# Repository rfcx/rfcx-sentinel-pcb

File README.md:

#RFCx Sentinel PCB
@gibsjose @jesse-millwood @rfcx

##Description
This repository contains the **KiCAD** project and related libraries for the RFCx PCB designed by Jesse Millwood and Joe Gibson for the GVSU (Grand Valley State University) RFCx Senior Project design, *Project Necromancer*. This project has been continued by Jesse Millwood and Joe Gibson after they graduated and has since been renamed *RFCx Sentinel*. 

This repository is for the main board that includes the following functionality:
- Buck/Boost input voltage to charge phone
- Regulate input power 3.3V to run the logic on the board
- Charge two Lithium Ion Batteries
- Take local measurements such as voltage, current, temperature, and humidity
- Relay information to the phone via a USB interface
- An experimental breakaway board for microphone filtering

This README is meant to be a user guide for the **REV 3** main board. 

###Revision Overview
Rev1 of the board was a single board and was designed for one particular off-the-shelf enclosure.
Rev2 of the design is a modular design in order to introduce a degree of flexibility to the design. This revision included an MPPT board and main board.
Rev3 of the design will keep the modular design, however new components will be chosen based on testing of Rev2. This revision is just the main board.

##Physical Install Instructions
The enclosure that is being used is the Polycase WP-33. The installer must take into consideration where the interfacing wires will be in relation to the other board. A list of interfacing wires that must be considered are:
* **Main Board:** Power from the panels.
* **Main Board:** 2 JST connectors that go from the batter charging circuitry to the batteries
* **Main Board:** 2 JST connectors that interface to the NTC thermocouple. This thermocouple is meant to be glued or attached to the batteries.
* **Main Board:** 1 USBA to microUSB connector to the phone
Once the hardware connections are made it will be a good idea to ensure that the phone has the proper software installed such as the proper ROM and version of the Gaurdian app. For phone software refer to the [RFCx Guardian App](https://github.com/rfcx/rfcx-guardian-android) github page.

##Outline of Directories
.  
├── Images  
│   ├── *Contains Images for the README*  
├── Kicad Project  
│   ├── Graphics  
│   │   ├── *Contains Graphics for the silk screen layer*  
│   ├── Graphics.pretty  
│   │   ├── *Contains `.kicad_mod` files to be placed on the silk screen layer*  
│   └── Main  
│       ├── *Contains schematic files (`.sch`) for the main board  
│       ├── Fabrication  
│       │   └── *Contains files for fabrication (Gerbers, BOM, Position, PDF)*  
│       │       Gerbers  
│       │       ├── *Contains Gerbers for the board manufacturers*  
│       │       Position  
│       │       ├── Inches  
│       │       │   ├── *Contains position file for top and bottom layers in inches*  
│       │       └── mm  
│       │           └── *Contains position file for top and bottom layers in mm*  
│       RFCx.pretty  
│       ├── *Contains module (footprint) files for components that needed to be made*  
│       Local-Libs  
│       └── *Contains schematic part libraries for parts that were made for this project*  
└── LICENSE  

## How to use this repository
1. Install KiCAD(4.0+) (http://kicad-pcb.org/download/)
2. clone the libraries and checkout a specific version
``` sh
mkdir -p ~/build
cd ~/build
git clone https://github.com/KiCad/kicad-library.git
cd kicad-library
git checkout 3c84dba8e473a325a17eae25ed3203d949589c10
mkdir build
cd build
cmake ..
make
make install
```
- A specific version of the KiCAD schematic libraries is used because sometimes they change. It is just safer to stick with one version though so there is little to no need to mess with the schematic symbols later
3. Download KiCAD footprints
4. Open the KiCAD application and load the project file.
- `File`-> `Open Project`
5. Open the `Mainboard.sch` file.
6. Tell KiCAD where the schematic symbol libraries are
- `Preferences`->`Component Libraries`
- Click the lower `Add` button and search for the `Local-Libs` directory if not already listed in the bottom pane of the window.
- Click the upper `Add` button and change to the `Local-Libs` directory. Select all of the `.lib` files and hit `Open`
- Click `Okay`

## Conventions for this project
- **Schematic Libraries:** The symbols in the `Local-Libs` libraries are to be used first. This is because I like how these symbols look. If the symbol is not there, use the symbols in `kicad-library`. If the symbol you are looking for isn't in any of those, make it your self, add it to the `Local-Libs` and make not of it in a pull request.
- **Footprint Libraries:** 
- **PCB Canvas:** Editing of the PCB should be done in the GAL mode of `pcbnew`. This is because some things are handled slightly differently in the other canvases.
- **
- **Units:** Use Imperial units when editing/laying out so an object/trace is not located at some odd fraction of an inch.

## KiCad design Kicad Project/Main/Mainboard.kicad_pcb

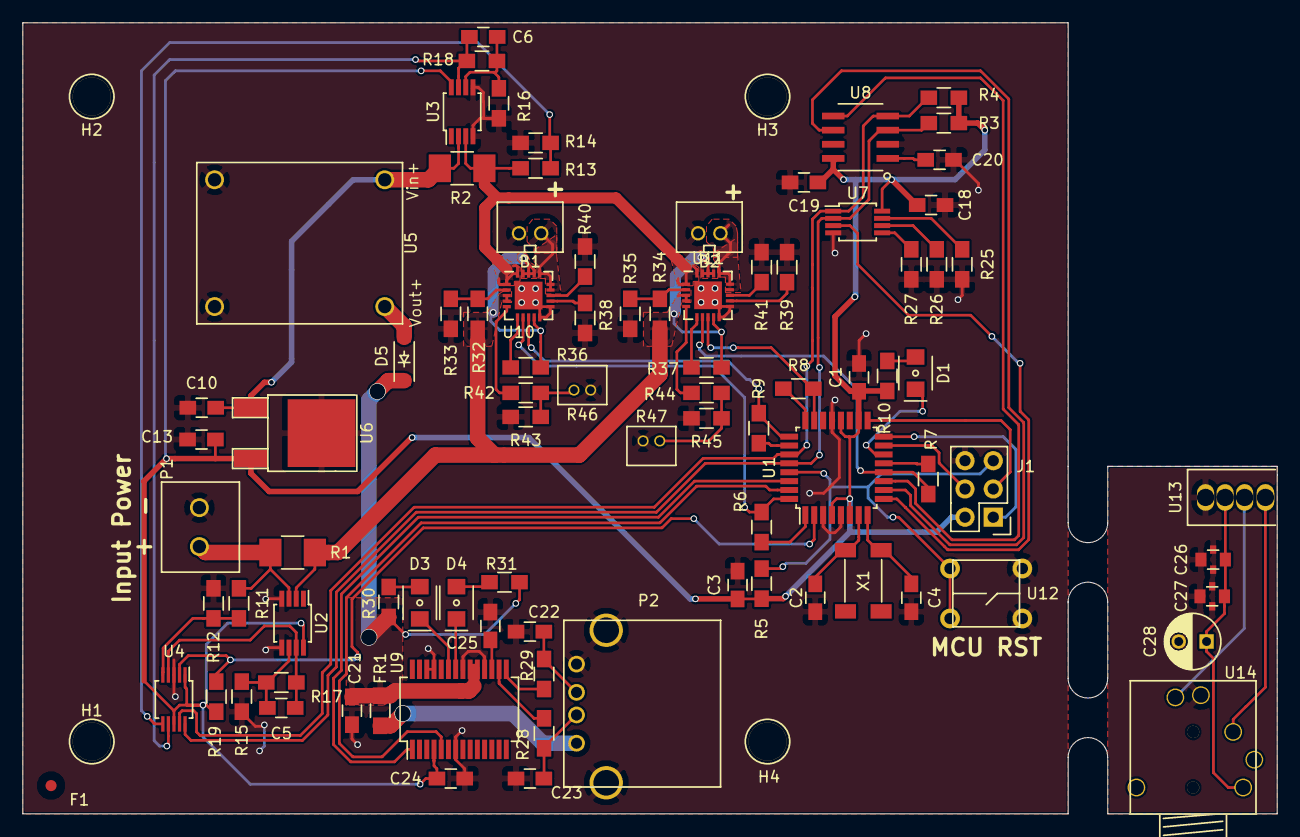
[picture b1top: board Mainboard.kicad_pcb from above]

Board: 2 copper layers, 112.8 x 71.1 mm, 91 parts (0 on the bottom side), 69 nets.

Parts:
B1, B2: Li-ion-2Cell-Conn; JST-2mm
C1, C3, C10, C13: 1uF; C_0805_HandSoldering
C2, C4: 6pF; C_0805_HandSoldering
C5, C6, C18, C20, C21, C24, C25: 0.1uF; C_0805_HandSoldering
C19: 0.22uF; C_0805_HandSoldering
C22, C23: 47pF; C_0805_HandSoldering
C26, C27: Cap-X2Y; C_0805_X2Y
C28: DNP; C_Radial_D5_L6_P2.5
D1: LED; LED-1208
D3: GRN; LED-1208
D4: YLW; LED-1208
D5: RB161M-20; SOD-123
F1: Fiducial; Fiducial_1mm_Dia_2.54mm_Outer_CopperTop
FR1: Ferrite; R_0805_HandSoldering
H1, H2, H3, H4: Mounting_Hole; Mnt_Hole
J1: ICSP; Pin_Header_Straight_2x03
P1: CONN_01X02; TerminalBlock_2
P2: USB_A
R1, R2: 0.51, 1W; R_1210_HandSoldering
R3, R4: 4.7k; R_0805_HandSoldering
R5, R19, R25, R26, R27, R43, R45: 10k; R_0805_HandSoldering
R6, R7, R8, R9, R36, R37, R42, R44: 1k; R_0805_HandSoldering
R10: 730; R_0805_HandSoldering
R11, R13: 1540; R_0805_HandSoldering
R12, R14: 2100; R_0805_HandSoldering
R15, R16: 200k; R_0805_HandSoldering
R17, R18: 2550; R_0805_HandSoldering
R28, R29: 27; R_0805_HandSoldering
R30, R31: 270; R_0805_HandSoldering
R32, R34: 270k; R_0805_HandSoldering
R33, R35, R38, R39: 100k; R_0805_HandSoldering
R40, R41: 1.14k; R_0805_HandSoldering
R46, R47: NTC; JST-1.5mm
U1: ATmega328P; TQFP-32_7x7mm_Pitch0.8mm
U2, U3: LTC6800; MSOP-8_3x3mm_Pitch0.65mm
U4: ADS1015; MSOP-10_3x3mm_Pitch0.5mm
U5: DC-DC_Boost_Module
U6: SM72238; TO-252-2Lead
U7: LM75BDP; MSOP-8_3x3mm_Pitch0.65mm
U8: HIH6130; HIH-SOIC-8
U9: FT232R; SSOP-28_5.3x10.2mm_Pitch0.65mm
U10, U11: MCP73871; QFN-20-1EP_4x4mm_Pitch0.5mm
U12: Button_SPST_4; SPST_4
U13: 3.5mm-Male-TH; Audio_3.5mm_Male_TH
U14: 3.5mm-Female-TH; Audio_3.5mm_Feale_TH
X1: 32kHz; SOJ-4

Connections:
+3V3: C1.1, C3.1, C13.1, C18.1, C19.1, C24.1, J1.2, R3.1, R4.1, R5.1, R10.1, R19.1, U1.4, U1.6, U1.18, U1.20, U2.8, U3.8, U4.1, U4.8, U6.3, U7.8, U8.8, U9.4
+5V: C21.1, D5.1, FR1.1, R30.1, R31.1, U9.19, U9.20
/ADC/Input-Current-H: P1.1, R1.1, R11.1, U2.3
/ADC/Output-Current-L: C10.1, R2.1, U3.2, U5.3, U6.1
/Battery Charging/Bat-In: R1.2, R32.1, R34.1, R36.1, R37.1, U2.2, U10.3, U10.4, U10.9, U10.17, U10.18, U10.19, U11.3, U11.4, U11.9, U11.17, U11.18, U11.19
/Battery Charging/Bat-Out: R2.2, R13.1, U3.3, U10.1, U10.20, U11.1, U11.20
/Environment Sensors/ENV_AL_H: U1.11, U8.5
/Environment Sensors/ENV_AL_L: U1.10, U8.6
/Environment Sensors/ENV_OS: U1.9, U7.3
/Microcontroller/AT-Alert: R19.2, U1.2, U4.2
/Microcontroller/AT-BAT1-STAT1: R9.2, U1.25, U10.8
/Microcontroller/AT-BAT1-STAT2: R6.2, U1.32, U10.7
/Microcontroller/AT-BAT2-STAT1: R8.2, U1.23, U11.8
/Microcontroller/AT-BAT2-STAT2: R7.2, U1.12, U11.7
/Microcontroller/AT-RXD: U1.30, U9.1
/Microcontroller/AT-SCL: R3.2, U1.28, U4.10, U7.2, U8.3
/Microcontroller/AT-SDA: R4.2, U1.27, U4.9, U7.1, U8.4
/Microcontroller/AT-TXD: U1.31, U9.5
GND: B1.1, B2.1, C1.2, C2.2, C3.2, C4.2, C10.2, C13.2, C18.2, C19.2, C20.2, C21.2, C22.2, C23.2, C24.2, C25.2, C26.2, C26.3, C26.4, C27.2, C27.3, C27.4, C28.2, J1.6, P1.2, P2.4, P2.5, R12.2, R14.2, R15.2, R16.2, R25.1, R26.2, R27.2, R33.2, R35.2, R38.2, R39.2, R40.2, R41.2, R43.2, R45.2, R46.2, R47.2, U1.3, U1.5, U1.21, U2.4, U2.5, U3.4, U3.5, U4.3, U5.1, U5.4, U6.2, U7.4, U8.2, U9.7, U9.18, U9.21, U9.25, U9.26, U10.10, U10.11, U10.21, U11.10, U11.11, U11.21, U12.1, U12.2, U13.4, U14.1
unnamed: B1.2, U10.14, U10.15, U10.16
unnamed: B2.2, U11.14, U11.15, U11.16
unnamed: C2.1, U1.7, X1.1
unnamed: C4.1, U1.8, X1.4
unnamed: C5.1, R15.1, R17.1, U2.6
unnamed: C5.2, R17.2, U2.7, U4.4
unnamed: C6.1, R16.1, R18.1, U3.6
unnamed: C6.2, R18.2, U3.7, U4.7
unnamed: C20.1, U8.1
unnamed: C22.1, P2.3, R29.1
unnamed: C23.1, P2.2, R28.1
unnamed: C25.1, U9.17
unnamed: C26.1, C27.1, C28.1, U13.3, U14.4
unnamed: D1.1, U1.14
unnamed: D1.2, R10.2
unnamed: D3.1, U9.23
unnamed: D3.2, R30.2
unnamed: D4.1, U9.22
unnamed: D4.2, R31.2
unnamed: D5.2, U5.2
unnamed: FR1.2, P2.1
unnamed: J1.1, U1.16
unnamed: J1.3, U1.17
unnamed: J1.4, U1.15
unnamed: J1.5, R5.2, U1.29, U12.3, U12.4
unnamed: R6.1, U1.1
unnamed: R7.1, U1.13
unnamed: R8.1, U1.24
unnamed: R9.1, U1.26
unnamed: R11.2, R12.1, U4.5
unnamed: R13.2, R14.1, U4.6
unnamed: R25.2, U7.7
unnamed: R26.1, U7.6
unnamed: R27.1, U7.5
unnamed: R28.2, U9.16
unnamed: R29.2, U9.15
unnamed: R32.2, R33.1, U10.2
unnamed: R34.2, R35.1, U11.2
unnamed: R36.2, U10.6
unnamed: R37.2, U11.6
unnamed: R38.1, U10.12
unnamed: R39.1, U11.12
unnamed: R40.1, U10.13
unnamed: R41.1, U11.13
unnamed: R42.1, U10.5
unnamed: R42.2, R43.1, R46.1
unnamed: R44.1, U11.5
unnamed: R44.2, R45.1, R47.1
unnamed: U13.1, U14.2
unnamed: U13.2, U14.3

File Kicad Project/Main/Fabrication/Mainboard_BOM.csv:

"Project:","Mainboard"
"Tool:","kicad"
"Number of Parts ","91"
" "," "
"Reference","Quantity","Value","Package","Distributor","Distributor #"
"F1","1","Fiducial","Fiducials:Fiducial_1mm_Dia_2.54mm_Outer_CopperTop","DigiKey","NA"
"C26,C27","2","Cap-X2Y","RFCx:C_0805_X2Y","DigiKey","709-1010-1-ND"
"C28","1","DNP","Capacitors_ThroughHole:C_Radial_D5_L6_P2.5","DigiKey","NA"
"C2,C4","2","6pF","Capacitors_SMD:C_0805_HandSoldering","DigiKey","311-1095-1-ND"
"C23,C22","2","47pF","Capacitors_SMD:C_0805_HandSoldering","DigiKey","1276-1832-1-ND"
"C5,C6,C20,C18,C24,C21,C25","7","0.1uF","Capacitors_SMD:C_0805_HandSoldering","DigiKey","399-1167-1-ND"
"C19","1","0.22uF","Capacitors_SMD:C_0805_HandSoldering","DigiKey","587-1287-1-ND"
"C3,C1,C13,C10","4","1uF","Capacitors_SMD:C_0805_HandSoldering","DigiKey","1276-1275-1-ND"
"U14","1","3.5mm-Female-TH","RFCx:Audio_3.5mm_Feale_TH","DigiKey","CP-435107-ND"
"FR1","1","Ferrite","Resistors_SMD:R_0805_HandSoldering","DigiKey","587-1911-1-ND"
"R46,R47","2","NTC","RFCx:JST-1.5mm","DigiKey","BC2384-ND, 455-1657-ND"
"R2,R1","2","0.51, 1W","Resistors_SMD:R_1210_HandSoldering","DigiKey","RCWE.51FCT-ND"
"R29,R28","2","27","Resistors_SMD:R_0805_HandSoldering","DigiKey","P27ACT-ND"
"R30,R31","2","270","Resistors_SMD:R_0805_HandSoldering","DigiKey","311-270CRCT-ND"
"R10","1","730","Resistors_SMD:R_0805_HandSoldering","DigiKey","P732CCT-ND"
"R8,R9,R7,R6,R36,R42,R37,R44","8","1k","Resistors_SMD:R_0805_HandSoldering","DigiKey","P1.0KACT-ND"
"R40,R41","2","1.14k","Resistors_SMD:R_0805_HandSoldering","DigiKey","P1.15KCCT-ND"
"R11,R13","2","1540","Resistors_SMD:R_0805_HandSoldering","DigiKey","P1.54KCCT-ND"
"R12,R14","2","2100","Resistors_SMD:R_0805_HandSoldering","DigiKey","P2.10KCCT-ND"
"R17,R18","2","2550","Resistors_SMD:R_0805_HandSoldering","DigiKey","311-2.55KCRCT-ND"
"R3,R4","2","4.7k","Resistors_SMD:R_0805_HandSoldering","DigiKey","311-4.70KCRCT-ND"
"R5,R19,R25,R26,R27,R43,R45","7","10k","Resistors_SMD:R_0805_HandSoldering","DigiKey","P10KACT-ND"
"R38,R33,R39,R35","4","100k","Resistors_SMD:R_0805_HandSoldering","DigiKey","RHM100KCHCT-ND"
"R15,R16","2","200k","Resistors_SMD:R_0805_HandSoldering","DigiKey","P200KACT-ND"
"R32,R34","2","270k","Resistors_SMD:R_0805_HandSoldering","DigiKey","P270KCCT-ND"
"H1,H2,H3,H4","4","Mounting_Hole","RFCX:Mnt_Hole","DigiKey","NA"
"U13","1","3.5mm-Male-TH","RFCx:Audio_3.5mm_Male_TH","DigiKey","839-1239-ND"
"D1","1","LED","RFCx:LED-1208","DigiKey","160-1404-1-ND"
"D5","1","RB161M-20","Diodes_SMD:SOD-123","DigiKey","RB161M-20CT-ND"
"D3","1","GRN","RFCx:LED-1208","DigiKey","350-2885-ND"
"D4","1","YLW","RFCx:LED-1208","DigiKey","511-1275-1-ND"
"P1","1","CONN_01X02","RFCX:TerminalBlock_2","DigiKey","ED2740-ND"
"U1","1","ATmega328P","Housings_QFP:TQFP-32_7x7mm_Pitch0.8mm","DigiKey","ATMEGA328P-AU-ND"
"J1","1","ICSP","Pin_Headers:Pin_Header_Straight_2x03","DigiKey","S2011EC-03-ND"
"U12","1","Button_SPST_4","RFCx:SPST_4","DigiKey","450-1650-ND"
"U2,U3","2","LTC6800","Housings_SSOP:MSOP-8_3x3mm_Pitch0.65mm","DigiKey","LTC6800HMS8#PBF-ND"
"U4","1","ADS1015","Housings_SSOP:MSOP-10_3x3mm_Pitch0.5mm","DigiKey","296-25227-1-ND"
"U6","1","SM72238","TO_SOT_Packages_SMD:TO-252-2Lead","DigiKey","296-39811-5-ND "
"U5","1","DC-DC_Boost_Module","RFCx:DC-DC_Boost_Module","DigiKey","NA"
"U7","1","LM75BDP","Housings_SSOP:MSOP-8_3x3mm_Pitch0.65mm","DigiKey","568-4768-1-ND"
"U8","1","HIH6130","RFCx:HIH-SOIC-8","DigiKey","480-3651-1-ND "
"P2","1","USB_A","Connect:USB_A","DigiKey","UE27AC54100-ND"
"U9","1","FT232R","Housings_SSOP:SSOP-28_5.3x10.2mm_Pitch0.65mm","DigiKey","768-1007-1-ND"
"U10,U11","2","MCP73871","Housings_DFN_QFN:QFN-20-1EP_4x4mm_Pitch0.5mm","DigiKey","MCP73871-2CCI/ML-ND"
"B1,B2","2","Li-ion-2Cell-Conn","RFCx:JST-2mm","DigiKey","455-1704-ND"
"X1","1","32kHz","RFCX:SOJ-4","DigiKey","300-8744-1-ND"

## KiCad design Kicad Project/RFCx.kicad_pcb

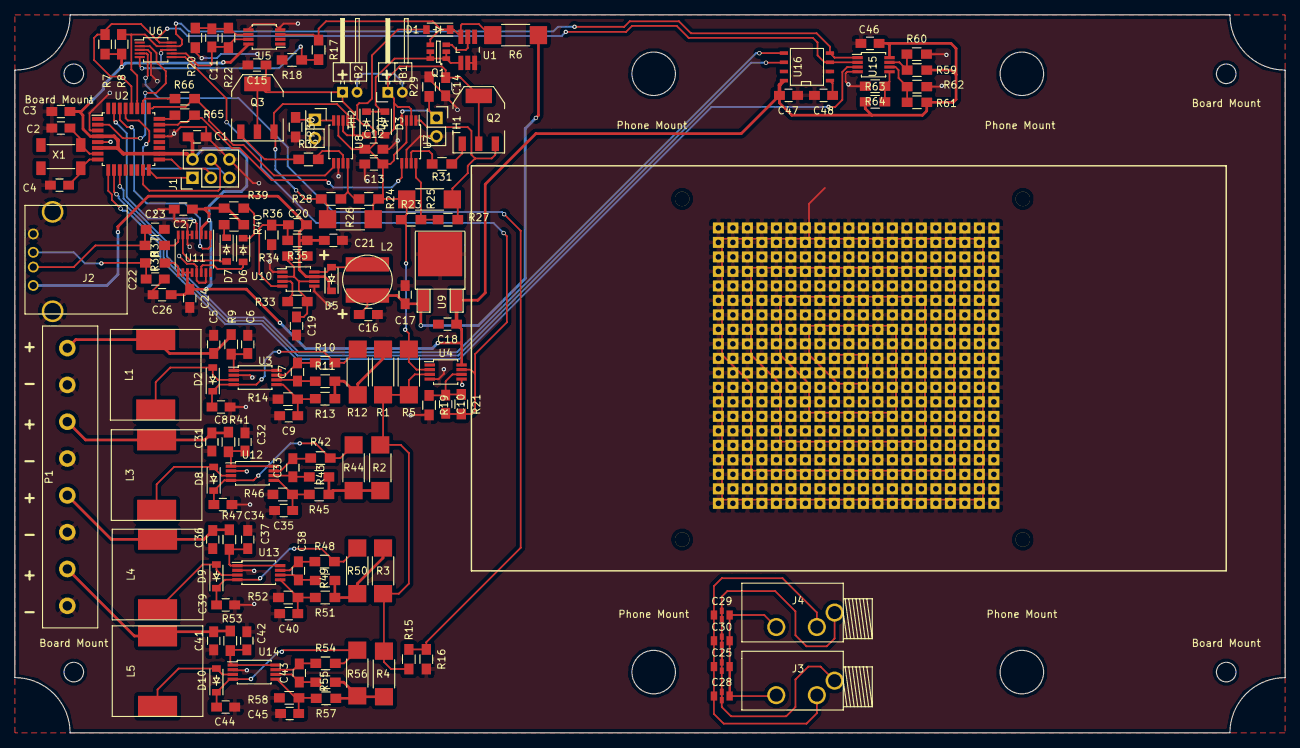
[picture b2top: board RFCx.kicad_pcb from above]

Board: 2 copper layers, 175.3 x 99.1 mm, 167 parts (1 on the bottom side), 96 nets.

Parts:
B1, B2: Li-ion(2Cell); Pin_Header_Angled_1x02
Board Mount: MountingHole_2-7mm
Board Mount#2, Board Mount#3, Board Mount#4: MountingHole_2-7mm
C1, C3, C7, C17, C18, C19, C33, C38, C43: 1uF; C_0805_HandSoldering
C2, C4: 10pF; C_0805_HandSoldering
C5, C6, C31, C32, C36, C37, C41, C42: 10uF; C_0805_HandSoldering
C8, C34, C39, C44: 22uF; C_0805_HandSoldering
C9, C35, C40, C45: 1nF; C_0805_HandSoldering
C10, C11, C12, C13, C14, C15, C46: 0.1uF; C_0805_HandSoldering
C16: 22uF Tant; C_0805_HandSoldering
C20: 39pF; C_0805_HandSoldering
C21: 68uF Tant; C_0805_HandSoldering
C22, C23: 47pF; C_0805_HandSoldering
C24, C26: 100nF; C_0805_HandSoldering
C25, C30: 0.1uF; X2Y
C27: 4.7uF; C_0805_HandSoldering
C28, C29: 1uF; X2Y
C47: 0.22uF; C_0805_HandSoldering
C48: 0.1; C_0805_HandSoldering
D1: 1N5819; SOD-123
D2, D3, D4, D5, D8, D9, D10: Diode-Shottky; SOD-123
D6: GRN; SOD-123
D7: LED; SOD-123
H1: Heatsink; HeatSink
J1: ICSP; Pin_Header_Straight_2x03
J2: USB; USB_A
J3, J4: Barrel; barrel-1-8
L1, L3, L4, L5: 27uH; Ind_12_5x12_5
L2: 6.8uH; Ind_6x6
P1: Terminal Block; Terminal_Block_8
Phone Mount: MountingHole_6mm
Phone Mount#2, Phone Mount#3, Phone Mount#4: MountingHole_6mm
Q1: FDC638; FDC-SOT-23-6
Q2, Q3: FZT788B; SOT-223
R1, R2, R3, R4: 0.025, 1W; R_2010_HandSoldering
R5, R6: 0.01,1W; R_2010_HandSoldering
R7, R8, R23, R24, R59, R60, R61, R62, R63, R64: 10k; R_0805_HandSoldering
R9, R10, R11, R31, R32, R41, R42, R43, R47, R48, R49, R53, R54, R55, R65, R66: 1k; R_0805_HandSoldering
R12, R44, R50, R56: 27.78, 1W; R_2010_HandSoldering
R13, R45, R51, R57: 2.32M; R_0805_HandSoldering
R14, R46, R52, R58: 845k; R_0805_HandSoldering
R15, R17: 1540; R_0805_HandSoldering
R16, R18: 2100; R_0805_HandSoldering
R19, R20, R33: 200k; R_0805_HandSoldering
R21: 2550; R_0805_HandSoldering
R22: Res; R_0805_HandSoldering
R25, R26: 0.2, 1W; R_2010_HandSoldering
R27, R28: 5k; R_0805_HandSoldering
R29, R30, R36: 49.9k; R_0805_HandSoldering
R34: 49.9; R_0805_HandSoldering
R35: 150k; R_0805_HandSoldering
R37, R38: 27; R_0805_HandSoldering
R39, R40: 730; R_0805_HandSoldering
TH1, TH2: NTC; Pin_Header_Straight_2x01
U1: LTC4412; TSOT-6-MK06A_Handsoldering
U2: ATmega328P; TQFP-32_7x7mm_Pitch0.8mm
U3, U12, U13, U14: SPV1040; TSSOP-8_4.4x3mm_Pitch0.65mm
U4, U5: LTC6800; MSOP-8_3x3mm_Pitch0.65mm
U6: ADS1015; MSOP-10_3x3mm_Pitch0.5mm
U7, U8: bq2057CTS; TSSOP-8_4.4x3mm_Pitch0.65mm
U9: SM72238; DPAK-2
U10: LMR61428; MSOP-8_3x3mm_Pitch0.65mm
U11: FT230X; SSOP-16_3.9x4.9mm_Pitch0.635mm
U15: LM75BDP; MSOP-8_3x3mm_Pitch0.65mm
U16: HIH6130; SOIC-8-N
X1: 32kHz; SOJ-4

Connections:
+3V3: C1.1, C3.1, C18.1, C24.1, C26.1, C27.1, C46.1, C47.1, J1.2, R7.1, R8.1, R39.1, R40.1, R59.1, R61.1, R63.1, U2.4, U2.6, U2.18, U4.8, U5.8, U6.8, U9.3, U11.3, U11.10, U11.11, U11.12, U15.8, U16.8
+5V: C20.1, C21.1, D5.1, J2.1, R34.1, R35.1, U10.7
/+3.3V and +5V Regulation/LM_FB: C20.2, R35.2, R36.1, U10.4
/+3.3V and +5V Regulation/Vin: C16.1, C17.1, L2.1, R6.1, U9.1
/ADC/Input-Current-H: R1.2, R2.2, R3.2, R4.2, R5.1, R15.1, U4.3
/ADC/Input-Current-L: C12.1, C13.1, D1.2, R5.2, R23.1, R24.1, R25.2, R26.2, U4.2, U7.3, U8.3
/ADC/Output-Current-H: D1.1, Q1.3, R6.2, R17.1, U1.6, U5.3
/Battery Management/Battery-Vout: D3.1, D4.1, Q1.1, U1.1
/Environment Sensors/ENV_AL_H: U2.11, U16.5
/Environment Sensors/ENV_AL_L: U2.10, U16.6
/Environment Sensors/ENV_OS: U2.9, U15.3
/MPPT1/MPPT-Vout: R1.1, R11.2, R12.2, R13.1
/MPPT1/Vin: C5.1, L1.1, P1.1, R9.1
/MPPT2/MPPT-Vout: R2.1, R43.2, R44.2, R45.1
/MPPT2/Vin: C31.1, L3.1, P1.3, R41.1
/MPPT3/MPPT-Vout: R3.1, R49.2, R50.2, R51.1
/MPPT3/Vin: C36.1, L4.1, P1.5, R47.1
/MPPT4/MPPT-Vout: R4.1, R55.2, R56.2, R57.1
/MPPT4/Vin: C41.1, L5.1, P1.7, R53.1
/Microcontroller/AT-Alert: U2.2, U6.2
/Microcontroller/AT-BAT1-STAT: R65.2, U2.23, U7.5
/Microcontroller/AT-BAT2-STAT: R66.2, U2.25, U8.5
/Microcontroller/AT-RXD: U2.30, U11.1
/Microcontroller/AT-SCL: R7.2, U2.28, U6.10, U15.2, U16.3
/Microcontroller/AT-SDA: R8.2, U2.27, U6.9, U15.1, U16.4
/Microcontroller/AT-TXD: U2.31, U11.4
/Phone Interface/Mic+: C25.1, C28.1, C29.1, C30.1, J3.3, J4.3
/Phone Interface/Mic-: C25.3, C28.3, C29.3, C30.3, J3.2, J4.2
/Phone Interface/MicShield: C25.2, C25.4, C28.2, C28.4, C29.2, C29.4, C30.2, C30.4, J3.1, J4.1
GND: B1.2, B2.2, C1.2, C2.2, C3.2, C4.2, C5.2, C6.2, C8.2, C9.2, C12.2, C13.2, C14.2, C15.2, C16.2, C17.2, C19.2, C21.2, C22.2, C23.2, C24.2, C26.2, C27.2, C31.2, C32.2, C34.2, C35.2, C36.2, C37.2, C39.2, C40.2, C41.2, C42.2, C44.2, C45.2, C46.2, C47.2, C48.2, H1.1, J1.6, J2.4, J2.5, J2.6, P1.2, P1.4, P1.6, P1.8, R14.2, R16.2, R18.2, R19.2, R20.2, R29.2, R30.2, R36.2, R46.2, R52.2, R58.2, R60.2, R62.2, R64.2, TH1.2, TH2.2, U1.2, U1.3, U2.3, U2.5, U2.21, U3.2, U4.4, U4.5, U5.4, U5.5, U6.3, U7.6, U8.6, U9.2, U10.1, U10.5, U11.5, U11.6, U11.13, U11.15, U12.2, U13.2, U14.2, U15.4, U16.2
unnamed: B1.1, C14.1, D3.2, Q2.2, Q2.4, U7.2
unnamed: B2.1, C15.1, D4.2, Q3.2, Q3.4, U8.2
unnamed: C2.1, U2.7, X1.1
unnamed: C4.1, U2.8, X1.4
unnamed: C6.1, R9.2, U3.1, U3.8
unnamed: C7.1, R11.1, U3.6
unnamed: C7.2, R10.1, U3.7
unnamed: C8.1, D2.1, R10.2, R12.1, U3.4
unnamed: C9.1, R13.2, R14.1, U3.5
unnamed: C10.1, R19.1, R21.1, U4.6
unnamed: C10.2, R21.2, U4.7, U6.6
unnamed: C11.1, R20.1, R22.1, U5.6
unnamed: C11.2, R22.2, U5.7, U6.7
unnamed: C19.1, R33.1, R34.2, U10.2, U10.6
unnamed: C22.1, J2.3, R38.1
unnamed: C23.1, J2.2, R37.1
unnamed: C32.1, R41.2, U12.1, U12.8
unnamed: C33.1, R43.1, U12.6
unnamed: C33.2, R42.1, U12.7
unnamed: C34.1, D8.1, R42.2, R44.1, U12.4
unnamed: C35.1, R45.2, R46.1, U12.5
unnamed: C37.1, R47.2, U13.1, U13.8
unnamed: C38.1, R49.1, U13.6
unnamed: C38.2, R48.1, U13.7
unnamed: C39.1, D9.1, R48.2, R50.1, U13.4
unnamed: C40.1, R51.2, R52.1, U13.5
unnamed: C42.1, R53.2, U14.1, U14.8
unnamed: C43.1, R55.1, U14.6
unnamed: C43.2, R54.1, U14.7
unnamed: C44.1, D10.1, R54.2, R56.1, U14.4
unnamed: C45.1, R57.2, R58.1, U14.5
unnamed: C48.1, U16.1
unnamed: D2.2, L1.2, U3.3
unnamed: D5.2, L2.2, U10.8
unnamed: D6.1, R39.2
unnamed: D6.2, U11.14
unnamed: D7.1, R40.2
unnamed: D7.2, U11.7
unnamed: D8.2, L3.2, U12.3
unnamed: D9.2, L4.2, U13.3
unnamed: D10.2, L5.2, U14.3
unnamed: J1.1, U2.16
unnamed: J1.3, U2.17
unnamed: J1.4, U2.15
unnamed: J1.5, U2.29
unnamed: Q1.2, U1.5
unnamed: Q2.1, R31.1
unnamed: Q2.3, R25.1, R27.2, U7.1
unnamed: Q3.1, R32.1
unnamed: Q3.3, R26.1, R28.2, U8.1
unnamed: R15.2, R16.1, U6.4
unnamed: R17.2, R18.1, U6.5
unnamed: R23.2, R27.1, U7.8
unnamed: R24.2, R28.1, U8.8
unnamed: R29.1, TH1.1, U7.4
unnamed: R30.1, TH2.1, U8.4
unnamed: R31.2, U7.7
unnamed: R32.2, U8.7
unnamed: R33.2, U10.3
unnamed: R37.2, U11.8
unnamed: R38.2, U11.9
unnamed: R59.2, R60.1, U15.7
unnamed: R61.2, R62.1, U15.6
unnamed: R63.2, R64.1, U15.5
unnamed: R65.1, U2.24
unnamed: R66.1, U2.26

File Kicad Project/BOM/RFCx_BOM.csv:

"Project:","RFCx"
"Tool:","kicad"
"Number of Parts ","159"
" "," "
"Reference","Quantity","Value","Package","Distributor","Distributor #"
"Q1","1","FDC638","RFCX:FDC-SOT-23-6","DigiKey","FDC638PCT-ND"
"C2,C4","2","10pF","Capacitors_SMD:C_0805_HandSoldering","DigiKey","709-1168-1-ND "
"C3,C1,C7,C19,C18,C17,C33,C38,C43","9","1uF","Capacitors_SMD:C_0805_HandSoldering","DigiKey","1276-1275-1-ND"
"C5,C6,C31,C32,C36,C37,C41,C42","8","10uF","Capacitors_SMD:C_0805_HandSoldering","DigiKey","587-1312-1-ND"
"C8,C34,C39,C44","4","22uF","Capacitors_SMD:C_0805_HandSoldering","DigiKey","1276-1822-1-ND "
"C9,C35,C40,C45","4","1nF","Capacitors_SMD:C_0805_HandSoldering","DigiKey","399-1147-1-ND"
"C10,C11,C12,C14,C13,C15,C30,C25,C46","9","0.1uF","Capacitors_SMD:C_0805_HandSoldering","DigiKey","311-1245-1-ND"
"Q2,Q3","2","FZT788B","SMD_Packages:SOT-223","DigiKey","FZT788BCT-ND"
"C16","1","22uF Tant","Capacitors_SMD:C_0805_HandSoldering","DigiKey","511-1506-1-ND"
"C20","1","39pF","Capacitors_SMD:C_0805_HandSoldering","DigiKey","1276-1769-1-ND"
"C21","1","68uF Tant","Capacitors_SMD:C_0805_HandSoldering","DigiKey","478-8414-1-ND"
"C27","1","4.7uF","Capacitors_SMD:C_0805_HandSoldering","DigiKey","1276-1065-1-ND"
"C26,C24","2","100nF","Capacitors_SMD:C_0805_HandSoldering","DigiKey","311-1245-1-ND"
"C23,C22","2","47pF","Capacitors_SMD:C_0805_HandSoldering","DigiKey","1276-1832-1-ND"
"C29,C28","2","1uF","RFCX:X2Y","DigiKey","709-1108-1-ND"
"C48","1","0.1","Capacitors_SMD:C_0805_HandSoldering","DigiKey","311-1245-1-ND"
"C47","1","0.22uF","Capacitors_SMD:C_0805_HandSoldering","DigiKey","587-1287-1-ND"
"R5,R6","2","0.01,1W","Resistors_SMD:R_2010_HandSoldering","DigiKey","RHM.010ASCT-ND"
"R7,R8,R23,R24,R60,R62,R64,R63,R61,R59","10","10k","Resistors_SMD:R_0805_HandSoldering","DigiKey","P10KACT-ND"
"R1,R2,R3,R4","4","0.025, 1W","Resistors_SMD:R_2010_HandSoldering","DigiKey","RHM.010ASCT-ND"
"R65,R66,R10,R11,R9,R31,R32,R42,R43,R41,R48,R49,R47,R54,R55,R53","16","1k","Resistors_SMD:R_0805_HandSoldering","DigiKey","P1.0KACT-ND "
"R12,R44,R50,R56","4","27.78, 1W","Resistors_SMD:R_2010_HandSoldering","DigiKey","RHM.010ASCT-ND"
"R13,R45,R51,R57","4","2.32M","Resistors_SMD:R_0805_HandSoldering","DigiKey","P6.65KCCT-ND"
"R14,R46,R52,R58","4","845k","Resistors_SMD:R_0805_HandSoldering","DigiKey","P2.10KCCT-ND "
"R15,R17","2","1540","Resistors_SMD:R_0805_HandSoldering","DigiKey","P1.54KCCT-ND"
"R16,R18","2","2100","Resistors_SMD:R_0805_HandSoldering","DigiKey","P2.10KCCT-ND"
"R21","1","2550","Resistors_SMD:R_0805_HandSoldering","DigiKey","311-2.55KCRCT-ND"
"R19,R20,R33","3","200k","Resistors_SMD:R_0805_HandSoldering","DigiKey","P200KACT-ND"
"R22","1","Res","Resistors_SMD:R_0805_HandSoldering","DigiKey","311-2.55KCRCT-ND"
"R25,R26","2","0.2, 1W","Resistors_SMD:R_2010_HandSoldering","DigiKey","989-1049-1-ND"
"R29,R30,R36","3","49.9k","Resistors_SMD:R_0805_HandSoldering","DigiKey","P49.9KCCT-ND"
"R27,R28","2","5k","Resistors_SMD:R_0805_HandSoldering","DigiKey","P4.99KCCT-ND "
"R34","1","49.9","Resistors_SMD:R_0805_HandSoldering","DigiKey","P49.9KCCT-ND"
"R35","1","150k","Resistors_SMD:R_0805_HandSoldering","DigiKey","P150KCCT-ND"
"R39,R40","2","730","Resistors_SMD:R_0805_HandSoldering","DigiKey","P732CCT-ND"
"R38,R37","2","27","Resistors_SMD:R_0805_HandSoldering","DigiKey","P27ACT-ND"
"X1","1","32kHz","RFCX:SOJ-4","DigiKey","300-8744-1-ND"
"L1,L3,L4,L5","4","27uH","RFCX:Ind_12_5x12_5","DigiKey","SRR1260-270MCT-ND"
"L2","1","6.8uH","RFCX:Ind_6x6","DigiKey","SRN6045-6R8YCT-ND "
"H1","1","Heatsink","RFCX:HeatSink","DigiKey","NA"
"D1","1","1N5819","Diodes_SMD:SOD-123","DigiKey","1N5819HW-FDICT-ND"
"D2,D3,D4,D5,D8,D9,D10","7","Diode-Shottky","Diodes_SMD:SOD-123","DigiKey","1N5819HW-FDICT-ND"
"D6","1","GRN","Diodes_SMD:SOD-123","DigiKey","754-1939-1-ND"
"D7","1","LED","Diodes_SMD:SOD-123","DigiKey","511-1293-1-ND"
"B1,B2","2","Li-ion(2Cell)","Pin_Headers:Pin_Header_Angled_1x02","DigiKey","455-1704-ND"
"P1","1","Terminal Block","RFCX:Terminal_Block_8","DigiKey","ED2615-ND"
"U1","1","LTC4412","Housings_SOT-23_SOT-143_TSOT-6:TSOT-6-MK06A_Handsoldering","DigiKey","LTC4412ES6#TRPBFCT-ND"
"U2","1","ATmega328P","Housings_QFP:TQFP-32_7x7mm_Pitch0.8mm","DigiKey","ATMEGA328P-AU-ND"
"J1","1","ICSP","Pin_Headers:Pin_Header_Straight_2x03","DigiKey","S2011EC-03-ND"
"U3,U12,U13,U14","4","SPV1040","Housings_SSOP:TSSOP-8_4.4x3mm_Pitch0.65mm","DigiKey","NA"
"U4,U5","2","LTC6800","SSOP:MSOP-8_3x3mm_Pitch0.65mm","DigiKey","LTC6800HMS8#PBF-ND"
"U6","1","ADS1015","Housings_SSOP:MSOP-10_3x3mm_Pitch0.5mm","DigiKey","296-25227-1-ND"
"U7,U8","2","bq2057CTS","SSOP:TSSOP-8_4.4x3mm_Pitch0.65mm","DigiKey","296-25916-1-ND"
"TH1,TH2","2","NTC","Pin_Headers:Pin_Header_Straight_2x01","DigiKey","BC2384-ND"
"U10","1","LMR61428","SSOP:MSOP-8_3x3mm_Pitch0.65mm","DigiKey","LMR61428XMM/NOPBCT-ND"
"U9","1","SM72238","SMD_Packages:DPAK-2","DigiKey","296-39811-5-ND "
"U11","1","FT230X","Housings_SSOP:SSOP-16_3.9x4.9mm_Pitch0.635mm","DigiKey","768-1135-1-ND"
"J2","1","USB","Connect:USB_A","DigiKey","UE27AC54100-ND"
"J3,J4","2","Barrel","RFCX:barrel-1-8","DigiKey","SC1460-ND"
"U15","1","LM75BDP","SSOP:MSOP-8_3x3mm_Pitch0.65mm","DigiKey","568-4768-1-ND"
"U16","1","HIH6130","SMD_Packages:SOIC-8-N","DigiKey","480-3651-1-ND "

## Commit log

2015-05-17 Modified gitignore for KiCad (it was for Eagle), and updated the README
2015-05-17 Added 3D files, local libraries (Jesse's libraries), and the .pretty project files
2015-05-17 Added Application Notes and Components; PDFs describing each component and how to use them
2015-05-17 Adding KiCad project
2015-05-17 Added some previews of the PCB and updated the README
2015-07-13 Revision 2
2015-08-03 Updated hardware files from August 3 2015 Updated README
2015-08-16 Removed the TI battery management circuits and the LT power path management This was replaced with a microchip battery management IC to handle the power path management/load sharing and battery charg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
2015-08-31 Produced Fabircation outputs Finished RevC of Main board Removed MPPT Board from Kicad Project
2015-08-31 Version 3
2015-08-31 Created third revison of the mainboard Created manufacturing files for the mainboard Deleated the MPPT board project
2015-11-28 Revision 3 of Sentinal PCB major changes: - This is one PCB now - The MPPT circuitry has been taken off - Libraries have been moved around - The FTDI FT232R is being used - A buck boost regulator is 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
2015-11-30 Rev 3.1 - Added microphone filter schematic and board - Added new silkscreen identifiers - Added Reset button for microcontroller - Fixed Address pin on ADS1015, pulled it up - Created new Fabricatio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
2015-12-02 Edited JST footprints and updated board Small edits to READM
2015-12-07 Replaced DC-DC Switching circuit with a prebuilt module
